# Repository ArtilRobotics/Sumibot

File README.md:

# Sumibot
This is a library for the Arduino IDE that helps interface with the on-board hardware on the Sumibot robot.

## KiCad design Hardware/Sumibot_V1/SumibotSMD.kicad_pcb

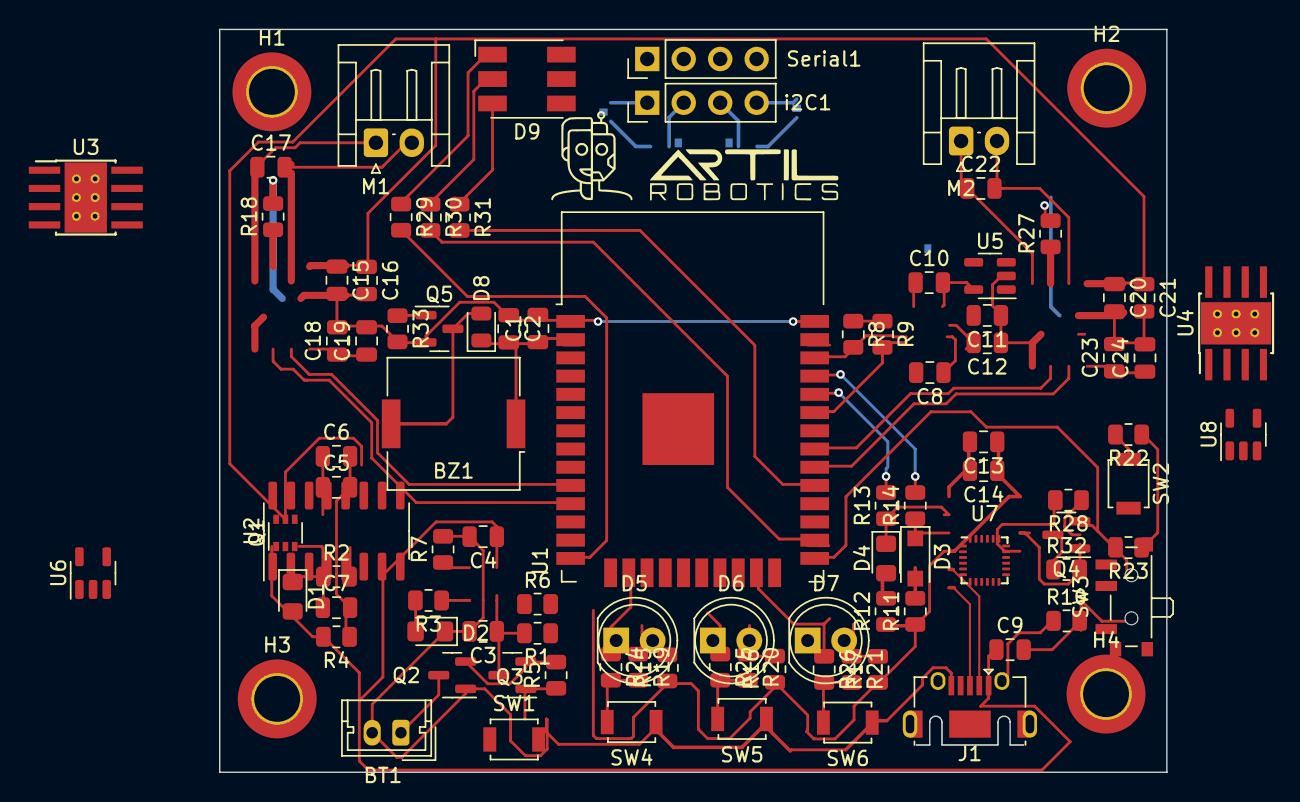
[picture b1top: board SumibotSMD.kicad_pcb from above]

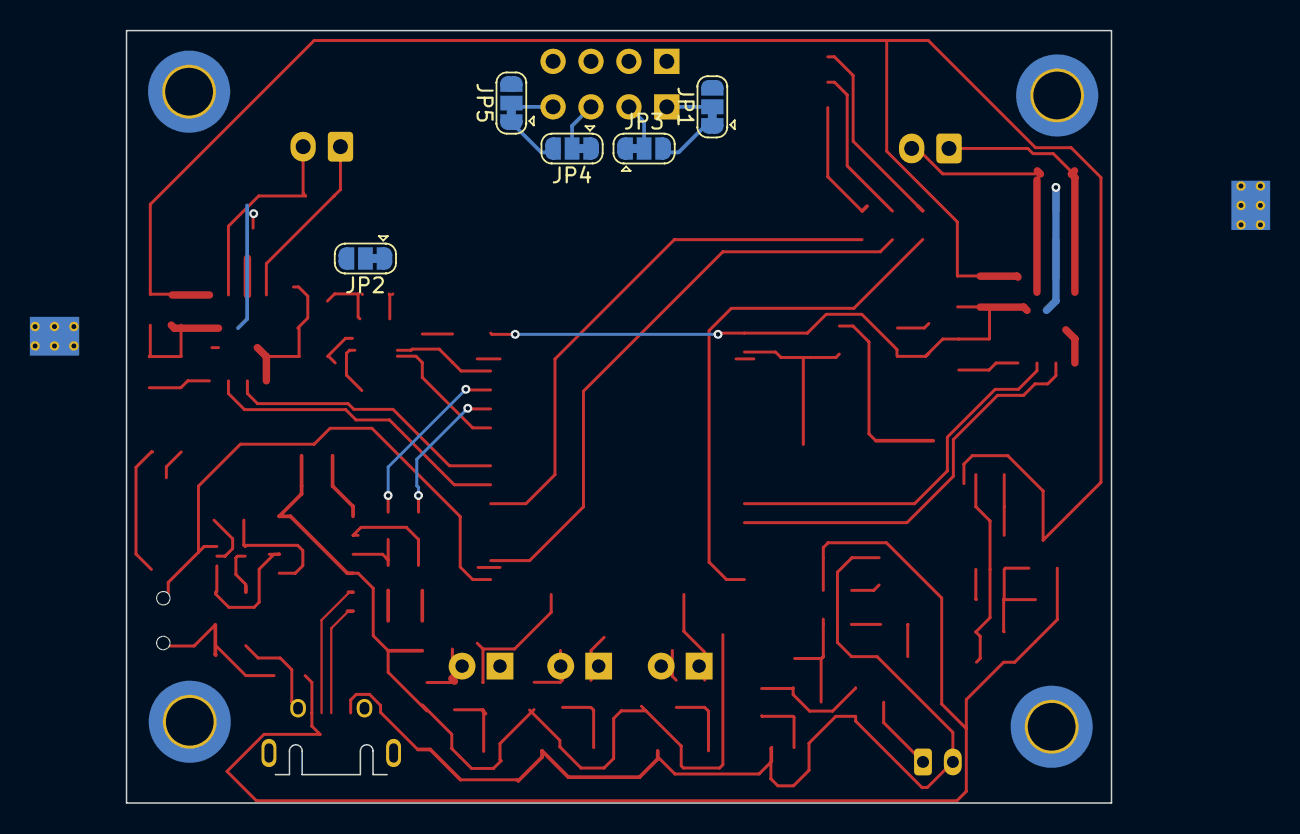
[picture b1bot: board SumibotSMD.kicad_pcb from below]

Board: 2 copper layers, 66.0 x 51.7 mm, 101 parts (5 on the bottom side), 67 nets.

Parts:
BT1: 2S; Molex_Micro-Latch_53253-0270_1x02_P2.00mm_Vertical
BZ1: Buzzer; Buzzer_Murata_PKMCS0909E
C1, C3, C4, C10, C15, C16, C17, C19, C20, C21: 10uF; C_0805_2012Metric
C2, C6, C9, C11, C14, C22, C24: 0.1uF; C_0805_2012Metric
C5: 10nF; C_0805_2012Metric
C7, C12: 47uF; C_0805_2012Metric
C8, C13: 3.3nF; C_0805_2012Metric
C18: 1uF; C_0805_2012Metric
C23: 2.2nF; C_0805_2012Metric
D1, D2: LED; LED_0805_2012Metric_Pad1.15x1.40mm_HandSolder
D3: MBR1020VL; D_SOD-123F
D4: Done; LED_0805_2012Metric_Pad1.15x1.40mm_HandSolder
D5: Verde; LED_D5.0mm
D6: Amarillo; LED_D5.0mm
D7: Rojo; LED_D5.0mm
D8: 1N4151; D_0805_2012Metric
D9: LED_RGBK; LED_RGB_5050-6
H1, H2, H3, H4: MountingHole; MountingHole_3.2mm_M3_ISO14580_Pad_TopBottom
J1: USB_B_Micro; USB_Micro-AB_Molex_47590-0001
JP1, JP2, JP3, JP4, JP5: I2C Ad; SolderJumper-3_P1.3mm_Bridged12_RoundedPad1.0x1.5mm
M1: Left; JST_EH_S2B-EH_1x02_P2.50mm_Horizontal
M2: Right; JST_EH_S2B-EH_1x02_P2.50mm_Horizontal
Q1: MBT3904DW1; SOT-363_SC-70-6
Q2, Q3, Q4: DMG2301L; SOT-23
Q5: DMG3406L; SOT-23
R1, R2, R13: 10K; R_0805_2012Metric
R3, R5, R6, R7, R14, R19, R20, R24, R25, R30, R31, R32: 1K; R_0805_2012Metric
R4: 0; R_0805_2012Metric
R8, R9: 100; R_0805_2012Metric
R10, R11: 0.2; R_0805_2012Metric
R12: 2M; R_0805_2012Metric
R15, R18, R33: 100K; R_0805_2012Metric
R16: 1M; R_0805_2012Metric
R17: 2K; R_0805_2012Metric
R21, R22, R26: 1.5K; R_0805_2012Metric
R23: 2.21K; R_0805_2012Metric
R27, R28, R29: 3K; R_0805_2012Metric
SW1: Reset; SW_SPST_B3U-1000P
SW2: Boot; SW_SPST_B3U-1000P
SW3: SW_SPDT; SW_SPDT_PCM12
SW4: A; SW_SPST_B3U-1000P
SW5: B; SW_SPST_B3U-1000P
SW6: C; SW_SPST_B3U-1000P
Serial1: 5V RX TX GND; PinHeader_1x04_P2.54mm_Vertical
U1: ESP32-WROOM-32
U2: CH340C; SOIC-16_3.9x9.9mm_P1.27mm
U3, U4: DRV8870DDA; Texas_HTSOP-8-1EP_3.9x4.9mm_P1.27mm_EP2.95x4.9mm_Mask2.4x3.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
U5: MCP73831-3-OT; SOT-23-5
U6: AP2112K-3.3; SOT-23-5
U7: MPU-9250; InvenSense_QFN-24_3x3mm_P0.4mm
U8: LP2985-3.3; SOT-23-5
i2C1: 5V GND SCL SDA; PinHeader_1x04_P2.54mm_Vertical

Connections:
+3V3: BZ1.1 (-), C1.1, C2.2, C4.1, C5.1, C18.1, C19.1, C22.2, D8.1 (K), JP1.1 (A), JP2.3 (B), JP5.3 (B), R1.1, R2.1, R6.1, R7.1, R19.1, R20.1, R21.1, R22.1, R23.1, U1.2 (VDD), U2.4 (V3), U2.16 (VCC), U6.5 (VOUT), U7.13 (VDD), U8.5 (VOUT)
+3V8: C9.1, C10.1, C14.1, C15.1, U3.4 (VREF), U4.4 (VREF)
+9V: BT1.1 (+), Q3.3 (D)
+BATT: C6.1, C7.1, C11.1, C12.1, C16.1, Q2.3 (D), Q4.3 (D), R12.2, U3.5 (VM), U4.5 (VM), U5.3 (VBAT)
/Brain/BattMeter: R12.1, R16.2, U1.7 (IO35)
/Brain/D+: J1.2 (D-), U2.5 (UD+)
/Brain/D-: J1.3 (D+), U2.6 (UD-)
/Brain/PWM_IN1A: U1.10 (IO25), U3.3 (IN1)
/Brain/PWM_IN1B: U1.30 (IO18), U4.3 (IN1)
/Brain/PWM_IN2A: U1.11 (IO26), U3.2 (IN2)
/Brain/PWM_IN2B: U1.31 (IO19), U4.2 (IN2)
/Brain/Reset: R1.2, SW1.2
/Brain/SCL: JP3.1 (A), JP4.3 (B), U1.36 (IO22)
/Brain/SDA: JP3.3 (B), JP4.1 (A), U1.33 (IO21)
/Motors/A01: C8.2, M1.2 (-), U3.6 (OUT1)
/Motors/A02: C8.1, M1.1 (+), U3.8 (OUT2)
/Motors/B01: C13.2, M2.2 (-), U4.6 (OUT1)
/Motors/B02: C13.1, M2.1 (+), U4.8 (OUT2)
/OutPuts/Buzzer: Q5.1 (G), R33.1
/Sensors/IO1: D5.1 (K), R27.1
/Sensors/IO2: D6.1 (K), R28.1
/Sensors/IO3: D7.1 (K), R29.1
/Sensors/SCL: R19.2, U7.23 (SCL/SCLK)
/Sensors/SDA: R20.2, U7.24 (SDA/MOSI)
Boot: Q1.3 (C2), R2.2, SW2.2, U1.25 (IO0)
DTR: Q1.4 (E2), R3.2, U2.13 (~DTR)
EN: Q1.6 (C1), U1.3 (EN)
GND: BT1.2 (-), C1.2, C2.1, C3.2, C4.2, C5.2, C6.2, C7.2, C9.2, C10.2, C11.2, C12.2, C14.2, C15.2, C16.2, C17.2, C18.2, C19.2, C20.2, C21.2, C22.1, C23.1, C24.1, D4.1 (K), D9.4 (K), J1.5 (GND), JP1.3 (B), JP2.1 (A), JP5.1 (A), Q3.1 (G), Q5.2 (S), R4.2, R10.2, R11.2, R15.1, R16.1, R17.2, R33.2, SW1.1, SW2.1, SW3.3 (C), SW4.1, SW5.1, SW6.1, Serial1.4, U1.1 (GND), U1.15 (GND), U1.38 (GND), U1.39 (GND), U2.1 (GND), U3.1 (GND), U3.9 (GND), U4.1 (GND), U4.9 (GND), U5.2 (VSS), U6.2 (GND), U7.18 (GND), U8.2 (GND)
unnamed: BZ1.2 (+), D8.2 (A), Q5.3 (D)
unnamed: C20.1, D3.1 (K), Q2.2 (S), R13.1, U6.1 (VIN)
unnamed: C21.1, U7.8 (VDDIO)
unnamed: C24.2, U7.10 (REGOUT)
unnamed: D1.1 (K), R9.1, U2.3 (RXD)
unnamed: D1.2 (A), R6.2
unnamed: D2.1 (K), R8.1, U2.2 (TXD)
unnamed: D2.2 (A), R7.2
unnamed: D4.2 (A), R14.2
unnamed: D5.2 (A), R21.2, R24.1
unnamed: D6.2 (A), R22.2, R25.1
unnamed: D7.2 (A), R23.2, R26.1
unnamed: D9.1 (RA), R30.1
unnamed: D9.2 (GA), R31.1
unnamed: D9.3 (BA), R32.1
unnamed: J1.6 (Shield), R4.1
unnamed: JP1.2 (C), i2C1.1
unnamed: JP2.2 (C), i2C1.2
unnamed: JP3.2 (C), i2C1.3
unnamed: JP4.2 (C), i2C1.4
unnamed: JP5.2 (C), U7.9 (AD0/MISO)
unnamed: Q1.2 (B1), R3.1
unnamed: Q1.5 (B2), R5.1
unnamed: Q3.2 (S), Q4.2 (S), R18.2
unnamed: Q4.1 (G), R18.1, SW3.2 (B)
unnamed: R10.1, U3.7 (ISEN)
unnamed: R11.1, U4.7 (ISEN)
unnamed: R13.2, U6.3 (EN)
unnamed: R14.1, U5.1 (STAT)
unnamed: R17.1, U5.5 (PROG)
unnamed: R24.2, R27.2, SW4.2
unnamed: R25.2, R28.2, SW5.2
unnamed: R26.2, R29.2, SW6.2
RTS: Q1.1 (E1), R5.2, U2.14 (~RTS)
RX2: Serial1.2, U1.27 (IO16)
RXD: R9.2, U1.35 (TXD0/IO1)
TX2: Serial1.3, U1.28 (IO17)
TXD: R8.2, U1.34 (RXD0/IO3)
VBUS: C3.1, C17.1, D3.2 (A), J1.1 (VBUS), Q2.1 (G), R15.2, U5.4 (VDD), U8.1 (VIN)

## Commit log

2022-04-16 Agrege plantilla de Electronica desde KarakuriSMD
2022-04-16 borre backups
2022-04-16 agregue al gitignore los backups
2022-04-19 Aplique jerarquía para trabajar en colaborativo
2022-04-20 Añadi DAC_Speaker y renombre carpeta kicad
2022-04-24 repare el gitignore
2022-04-24 Elimine Backup de Kicad
2022-04-24 Incluyendo toggle
2022-04-26 Circuito toggle, diagrama kicad
2022-04-27 implementó on/off toggle switch
2022-06-28 segundo commit
